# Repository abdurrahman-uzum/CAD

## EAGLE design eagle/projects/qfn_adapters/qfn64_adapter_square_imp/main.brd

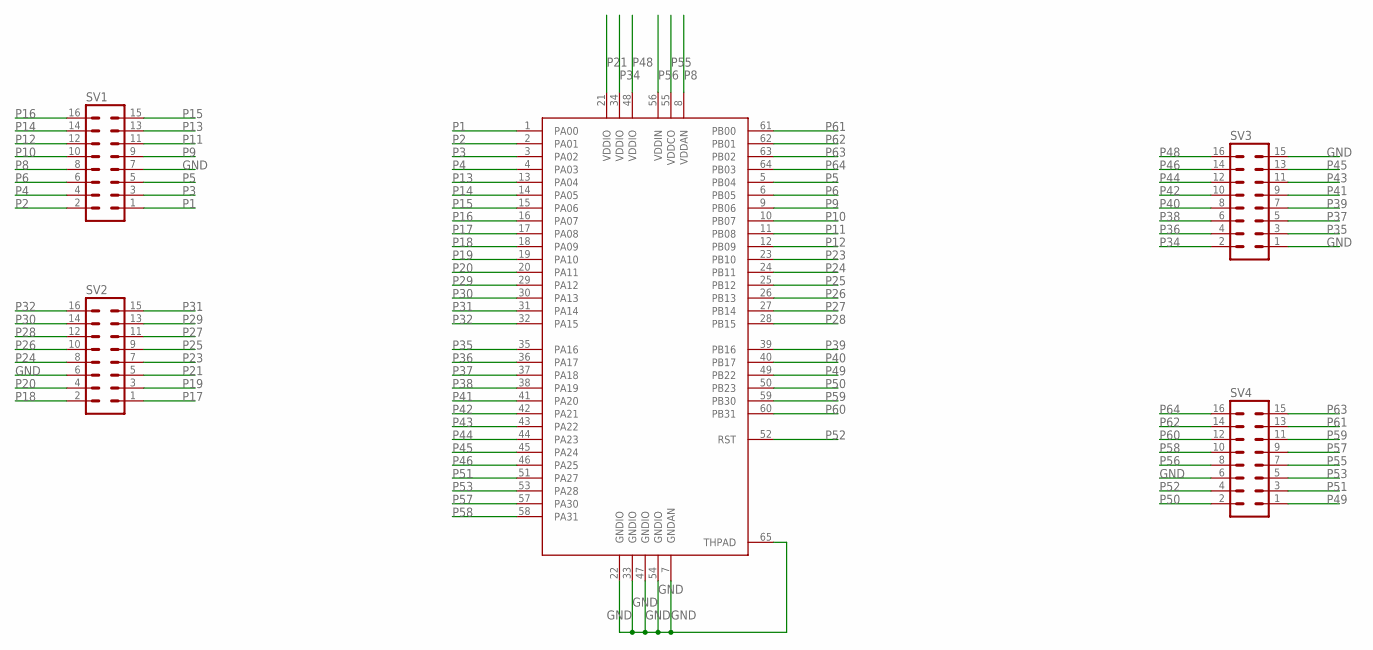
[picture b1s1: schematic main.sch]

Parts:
SV1, SV2, SV3, SV4: MA08-2
U$1: ATSAMD21J18AQFN64; QFN50P900X900X100-65T535

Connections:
GND: SV1.7, SV2.6, SV3.1, SV3.15, SV4.6, U$1.7 (GNDAN), U$1.22 (GNDIO), U$1.33 (GNDIO), U$1.47 (GNDIO), U$1.54 (GNDIO), U$1.65 (THPAD)
P1: SV1.1, U$1.1 (PA00)
P2: SV1.2, U$1.2 (PA01)
P3: SV1.3, U$1.3 (PA02)
P4: SV1.4, U$1.4 (PA03)
P5: SV1.5, U$1.5 (PB04)
P6: SV1.6, U$1.6 (PB05)
P8: SV1.8, U$1.8 (VDDAN)
P9: SV1.9, U$1.9 (PB06)
P10: SV1.10, U$1.10 (PB07)
P11: SV1.11, U$1.11 (PB08)
P12: SV1.12, U$1.12 (PB09)
P13: SV1.13, U$1.13 (PA04)
P14: SV1.14, U$1.14 (PA05)
P15: SV1.15, U$1.15 (PA06)
P16: SV1.16, U$1.16 (PA07)
P17: SV2.1, U$1.17 (PA08)
P18: SV2.2, U$1.18 (PA09)
P19: SV2.3, U$1.19 (PA10)
P20: SV2.4, U$1.20 (PA11)
P21: SV2.5, U$1.21 (VDDIO)
P23: SV2.7, U$1.23 (PB10)
P24: SV2.8, U$1.24 (PB11)
P25: SV2.9, U$1.25 (PB12)
P26: SV2.10, U$1.26 (PB13)
P27: SV2.11, U$1.27 (PB14)
P28: SV2.12, U$1.28 (PB15)
P29: SV2.13, U$1.29 (PA12)
P30: SV2.14, U$1.30 (PA13)
P31: SV2.15, U$1.31 (PA14)
P32: SV2.16, U$1.32 (PA15)
P34: SV3.2, U$1.34 (VDDIO)
P35: SV3.3, U$1.35 (PA16)
P36: SV3.4, U$1.36 (PA17)
P37: SV3.5, U$1.37 (PA18)
P38: SV3.6, U$1.38 (PA19)
P39: SV3.7, U$1.39 (PB16)
P40: SV3.8, U$1.40 (PB17)
P41: SV3.9, U$1.41 (PA20)
P42: SV3.10, U$1.42 (PA21)
P43: SV3.11, U$1.43 (PA22)
P44: SV3.12, U$1.44 (PA23)
P45: SV3.13, U$1.45 (PA24)
P46: SV3.14, U$1.46 (PA25)
P48: SV3.16, U$1.48 (VDDIO)
P49: SV4.1, U$1.49 (PB22)
P50: SV4.2, U$1.50 (PB23)
P51: SV4.3, U$1.51 (PA27)
P52: SV4.4, U$1.52 (RST)
P53: SV4.5, U$1.53 (PA28)
P55: SV4.7, U$1.55 (VDDCO)
P56: SV4.8, U$1.56 (VDDIN)
P57: SV4.9, U$1.57 (PA30)
P58: SV4.10, U$1.58 (PA31)
P59: SV4.11, U$1.59 (PB30)
P60: SV4.12, U$1.60 (PB31)
P61: SV4.13, U$1.61 (PB00)
P62: SV4.14, U$1.62 (PB01)
P63: SV4.15, U$1.63 (PB02)
P64: SV4.16, U$1.64 (PB03)

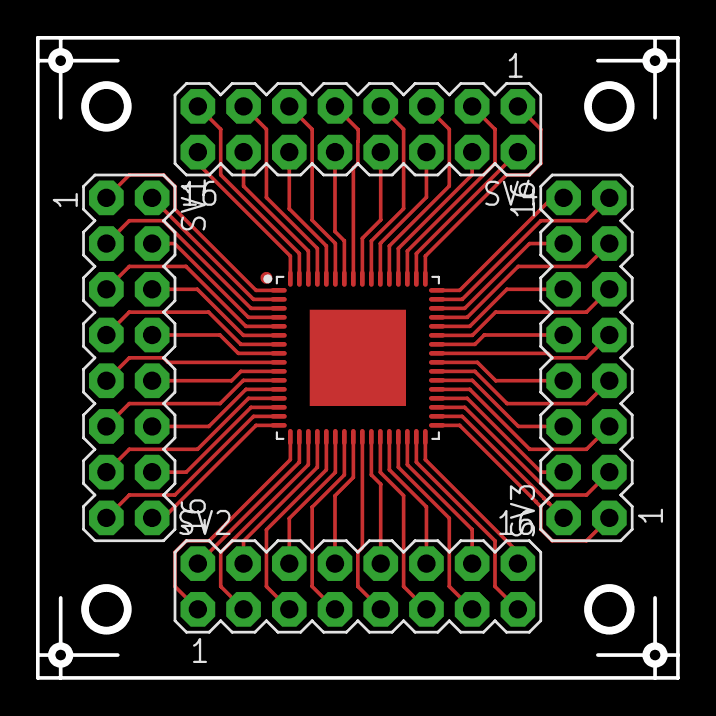
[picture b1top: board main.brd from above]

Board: 2 copper layers, 35.6 x 35.6 mm, 5 parts (0 on the bottom side), 60 nets.

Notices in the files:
parts and their libraries:
SparkFun-IC-Power: Licensing: Creative Commons ShareAlike 4.0 International - https://creativecommons.org/licenses/by-sa/4.0
